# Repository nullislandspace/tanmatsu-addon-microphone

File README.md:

# Tanmatsu add-on: Mono/stereo I2S microphone adapter

This repository contains the hardware design files for the I2S microphone adapter to use
ready-made ICS-43434 mini-PCBs (marked as MRS197A or similar) to the Tanmatsu

## License

The contents of this repository may be considered in the public domain or [CC0-1.0](https://creativecommons.org/publicdomain/zero/1.0) licensed at your disposal.

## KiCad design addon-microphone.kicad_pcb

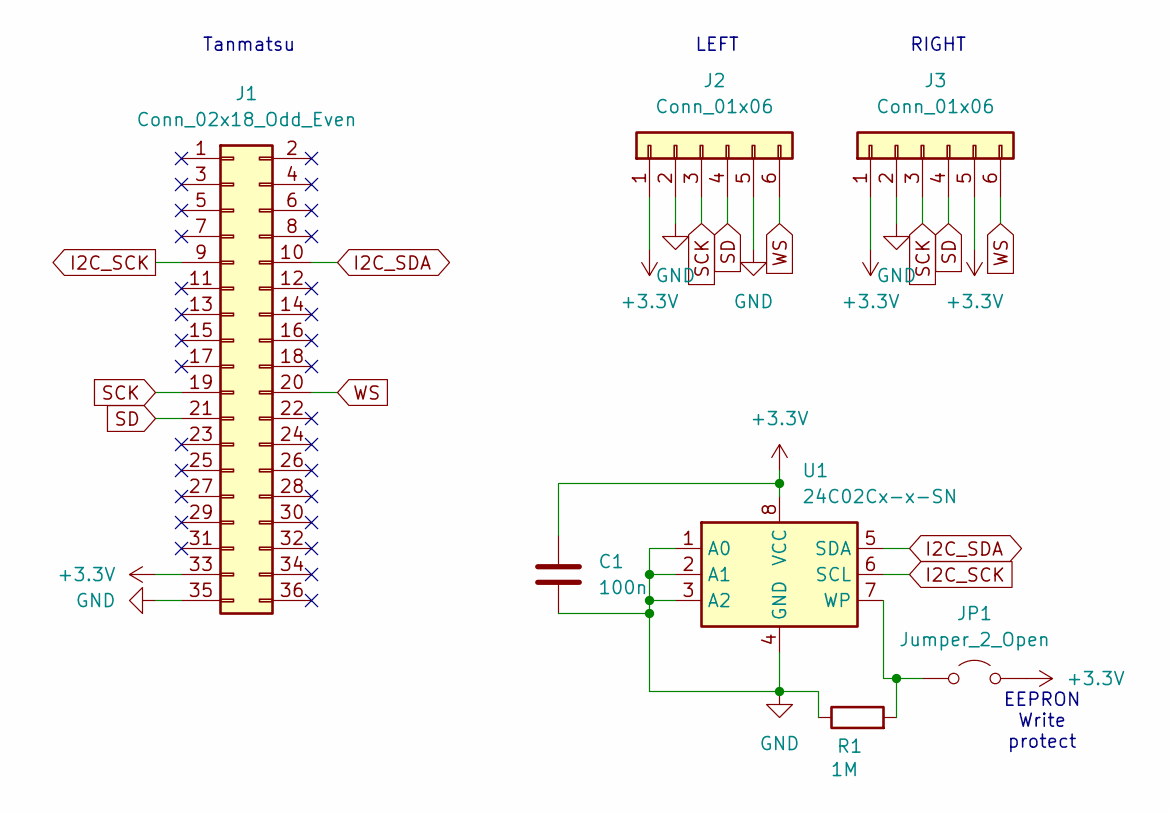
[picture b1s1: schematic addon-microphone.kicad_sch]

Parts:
C1: 100n; C_Disc_D5.0mm_W2.5mm_P5.00mm
J1: Conn_02x18_Odd_Even; PinHeader_2x18_P2.54mm_Vertical
J2, J3: Conn_01x06; PinHeader_1x06_P2.54mm_Vertical
JP1: Jumper_2_Open; SolderJumper-2_P1.3mm_Open_RoundedPad1.0x1.5mm
R1: 1M; R_Axial_DIN0204_L3.6mm_D1.6mm_P7.62mm_Horizontal
U1: 24C02Cx-x-SN; DIP-8_W7.62mm

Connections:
+3.3V: C1.1, J1.33, J2.1, J3.1, J3.5, JP1.2 (B), U1.8 (VCC)
GND: C1.2, J1.35, J2.2, J2.5, J3.2, R1.1, U1.1 (A0), U1.2 (A1), U1.3 (A2), U1.4 (GND)
I2C_SCK: J1.9, U1.6 (SCL)
I2C_SDA: J1.10, U1.5 (SDA)
unnamed: JP1.1 (A), R1.2, U1.7 (WP)
SCK: J1.19, J2.3, J3.3
SD: J1.21, J2.4, J3.4
WS: J1.20, J2.6, J3.6

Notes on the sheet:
RIGHT
LEFT
Tanmatsu
EEPRON Write protect

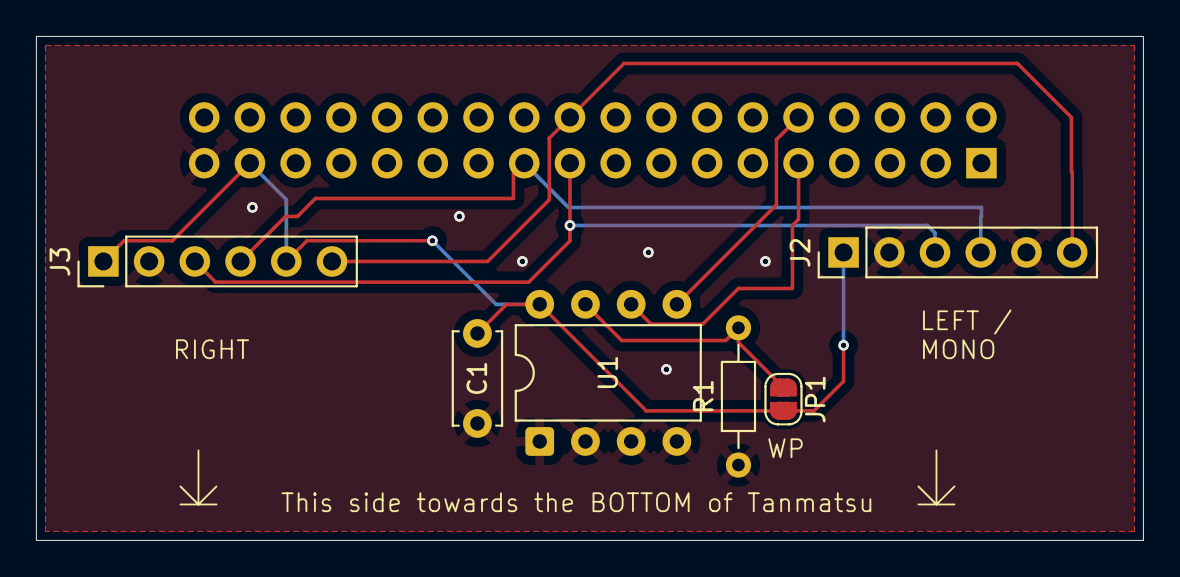
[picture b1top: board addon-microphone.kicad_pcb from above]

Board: 2 copper layers, 61.5 x 28.0 mm, 7 parts (1 on the bottom side), 8 nets.

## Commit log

2026-04-20 Initial checkin
2026-04-21 Add I2C EEPROM

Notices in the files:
addon-microphone.kicad_pcb:
(C) 2026 Rene Schickbauer
